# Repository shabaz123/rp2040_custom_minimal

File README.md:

# RP2040 Minimal Project for KiCad

This repository contains a modified version of the Raspberry Pi RP2040 Minimal design.

The modified version is more suited to recent KiCad versions (for instance KiCad 10), and it improves things slightly if the board is to be produced, for fewer 0402 parts rotating/sliding/tombstoning issues.

## Schematic

The schematic includes the RP2040 microcontroller along with supporting circuitry. The USB connector is USB-C, unlike the original Micro USB. 

**NOTE**: The GPIO connectors from the original schematic have been removed, so that the schematic is ready for custom additions.

## PCB Layout

The image here shows the top side copper. The bottom side is nearly all ground plane, apart from a few traces that carry 1.1V core power, and one at the USB-C connector end to allow cables to be inserted in any orientation.

## 3D Render

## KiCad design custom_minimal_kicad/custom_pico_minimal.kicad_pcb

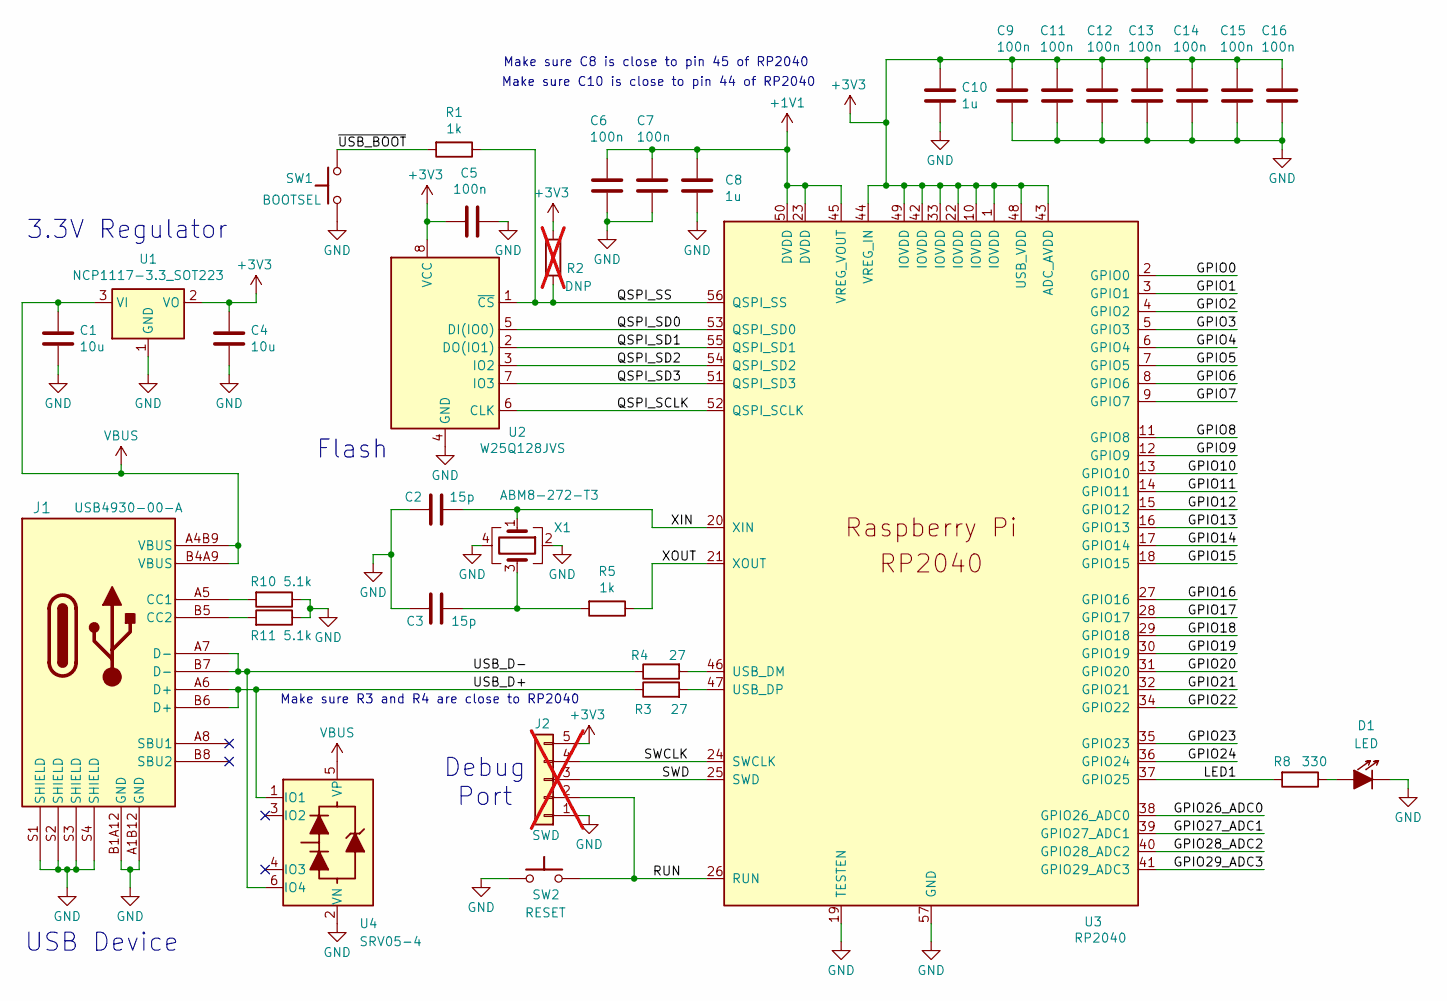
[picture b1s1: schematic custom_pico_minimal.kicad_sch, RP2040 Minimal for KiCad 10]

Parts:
C1, C4: 10u; C_0805_2012Metric; LCSC Part # C126586
C2, C3: 15p; 0402-footprint-improved-Cap3D; LCSC Part # C76950
C5, C6, C7, C9, C11, C12, C13, C14, C15, C16: 100n; 0402-footprint-improved-Cap3D; LCSC Part # C152814
C8, C10: 1u; 0402-footprint-improved-Cap3D; LCSC Part # C88945
D1: LED; LED_0805_2012Metric; LCSC Part # C2297
J1: USB4930-00-A; CONN_USB4930-00-A_GCT; LCSC Part # C2988369
J2: SWD; PinHeader_1x05_P2.54mm_Vertical; not fitted
R1, R5: 1k; 0402-footprint-improved-Res3D; LCSC Part # C852624
R2: DNP; 0402-footprint-improved-Res3D; not fitted
R3, R4: 27; 0402-footprint-improved-Res3D; LCSC Part # C384351
R8: 330; 0402-footprint-improved-Res3D; LCSC Part # C71626
R10, R11: 5.1k; 0402-footprint-improved-Res3D; LCSC Part # C723526
SW1: BOOTSEL; Tact-SW-TS-1101-6mm-3.6mm; LCSC Part # C500065
SW2: RESET; Tact-SW-TS-1101-6mm-3.6mm; LCSC Part # C500065
U1: NCP1117-3.3_SOT223; SOT-223-3_TabPin2; LCSC Part # C26537
U2: W25Q128JVS; SOIC-8_5.3x5.3mm_P1.27mm; LCSC Part # C97521
U3: RP2040; RP2040-QFN-56; LCSC Part # C2040
U4: SRV05-4; SOT23-6-SRV05-04; LCSC Part # C2836319
X1: ABM8-272-T3; Crystal_SMD_3225-4Pin_3.2x2.5mm; LCSC Part # C20625731

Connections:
+1V1: C6.1, C7.1, C8.1, U3.23 (DVDD), U3.45 (VREG_VOUT), U3.50 (DVDD)
+3V3: C4.1, C5.1, C9.1, C10.1, C11.1, C12.1, C13.1, C14.1, C15.1, C16.1, J2.5, R2.1, U1.2 (VO), U2.8 (VCC), U3.1 (IOVDD), U3.10 (IOVDD), U3.22 (IOVDD), U3.33 (IOVDD), U3.42 (IOVDD), U3.43 (ADC_AVDD), U3.44 (VREG_IN), U3.48 (USB_VDD), U3.49 (IOVDD)
/GPIO0: U3.2 (GPIO0)
/GPIO1: U3.3 (GPIO1)
/GPIO2: U3.4 (GPIO2)
/GPIO3: U3.5 (GPIO3)
/GPIO4: U3.6 (GPIO4)
/GPIO5: U3.7 (GPIO5)
/GPIO6: U3.8 (GPIO6)
/GPIO7: U3.9 (GPIO7)
/GPIO8: U3.11 (GPIO8)
/GPIO9: U3.12 (GPIO9)
/GPIO10: U3.13 (GPIO10)
/GPIO11: U3.14 (GPIO11)
/GPIO12: U3.15 (GPIO12)
/GPIO13: U3.16 (GPIO13)
/GPIO14: U3.17 (GPIO14)
/GPIO15: U3.18 (GPIO15)
/GPIO16: U3.27 (GPIO16)
/GPIO17: U3.28 (GPIO17)
/GPIO18: U3.29 (GPIO18)
/GPIO19: U3.30 (GPIO19)
/GPIO20: U3.31 (GPIO20)
/GPIO21: U3.32 (GPIO21)
/GPIO22: U3.34 (GPIO22)
/GPIO23: U3.35 (GPIO23)
/GPIO24: U3.36 (GPIO24)
/GPIO26_ADC0: U3.38 (GPIO26_ADC0)
/GPIO27_ADC1: U3.39 (GPIO27_ADC1)
/GPIO28_ADC2: U3.40 (GPIO28_ADC2)
/GPIO29_ADC3: U3.41 (GPIO29_ADC3)
/LED1: R8.2, U3.37 (GPIO25)
/QSPI_SCLK: U2.6 (CLK), U3.52 (QSPI_SCLK)
/QSPI_SD0: U2.5 (DI(IO0)), U3.53 (QSPI_SD0)
/QSPI_SD1: U2.2 (DO(IO1)), U3.55 (QSPI_SD1)
/QSPI_SD2: U2.3 (IO2), U3.54 (QSPI_SD2)
/QSPI_SD3: U2.7 (IO3), U3.51 (QSPI_SD3)
/QSPI_SS: R1.1, R2.2, U2.1 (~CS), U3.56 (QSPI_SS)
/RUN: J2.2, SW2.2, U3.26 (RUN)
/SWCLK: J2.4, U3.24 (SWCLK)
/SWD: J2.3, U3.25 (SWD)
/USB_D+: J1.A6 (D+), J1.B6 (D+), R3.1, U4.1 (IO1)
/USB_D-: J1.A7 (D-), J1.B7 (D-), R4.1, U4.6 (IO4)
/XIN: C2.1, U3.20 (XIN), X1.1
/XOUT: R5.1, U3.21 (XOUT)
/~USB_BOOT: R1.2, SW1.2
GND: C1.2, C2.2, C3.2, C4.2, C5.2, C6.2, C7.2, C8.2, C9.2, C10.2, C11.2, C12.2, C13.2, C14.2, C15.2, C16.2, D1.1 (K), J1.A1B12 (GND), J1.B1A12 (GND), J1.S1 (SHIELD), J1.S2 (SHIELD), J1.S3 (SHIELD), J1.S4 (SHIELD), J2.1, R10.1, R11.1, SW1.1, SW2.1, U1.1 (GND), U2.4 (GND), U3.19 (TESTEN), U3.57 (GND), U4.2 (VN), X1.2, X1.4
unnamed: C3.1, R5.2, X1.3
unnamed: D1.2 (A), R8.1
unnamed: J1.A5 (CC1), R10.2
unnamed: J1.B5 (CC2), R11.2
unnamed: R4.2, U3.46 (USB_DM)
unnamed: R3.2, U3.47 (USB_DP)
VBUS: C1.1, J1.A4B9 (VBUS), J1.B4A9 (VBUS), U1.3 (VI), U4.5 (VP)

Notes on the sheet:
3.3V Regulator
Make sure C8 is close to pin 45 of RP2040
USB Device
Make sure C10 is close to pin 44 of RP2040
Make sure R3 and R4 are close to RP2040
Debug Port
Flash

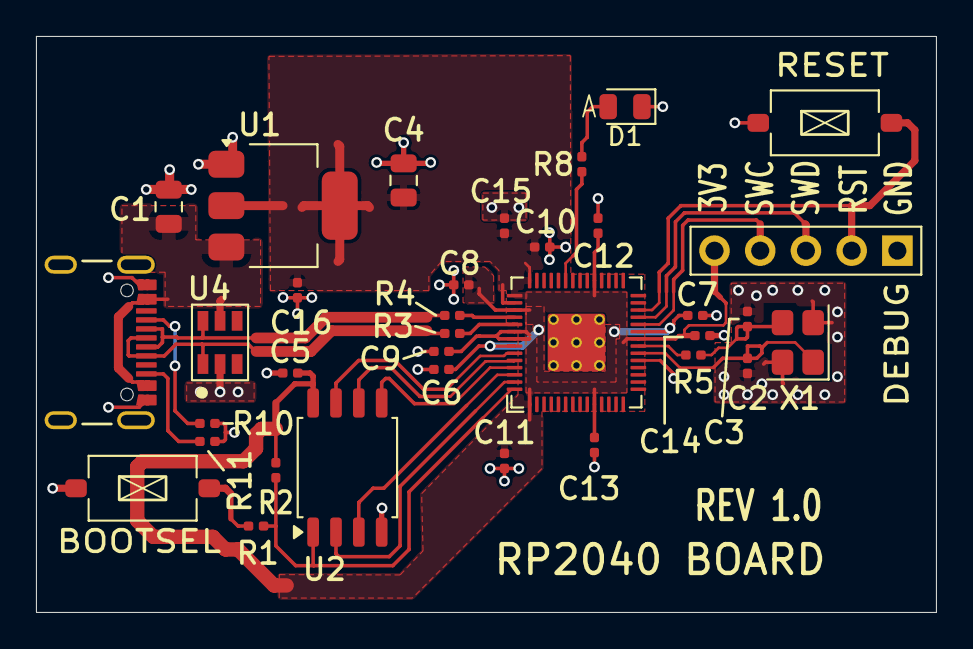
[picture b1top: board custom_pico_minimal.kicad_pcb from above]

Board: 2 copper layers, 50.0 x 32.0 mm, 34 parts (0 on the bottom side), 25 nets.

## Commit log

2026-06-27 Update README to add doc images with descriptive text
2026-06-27 Revise README for schematic and PCB layout details
    Updated schematic and PCB layout descriptions for clarity and accuracy.
2026-06-29 Fix description of PCB layout traces
    Corrected 'a few traces' to 'one trace' for accuracy.
